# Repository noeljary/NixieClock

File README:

# NixieClock

+ contents

- mcu_code:    firmware for nixie clock micro-controller
- schematics:  eagle circuit schematics and pcb designs including pdf versions
- parts_lists: details of all parts required for circuits

+ description

design and implementation data for the nixie clock project, repository includes data relating to the hardware circuit schematic and board design, supplemented by production gerber files and 3d models

code is available for the microcontroller firmware which runs the interface between the clock ic and the nixie tubes and also for the computer backend which will allow for administrative control of the clock

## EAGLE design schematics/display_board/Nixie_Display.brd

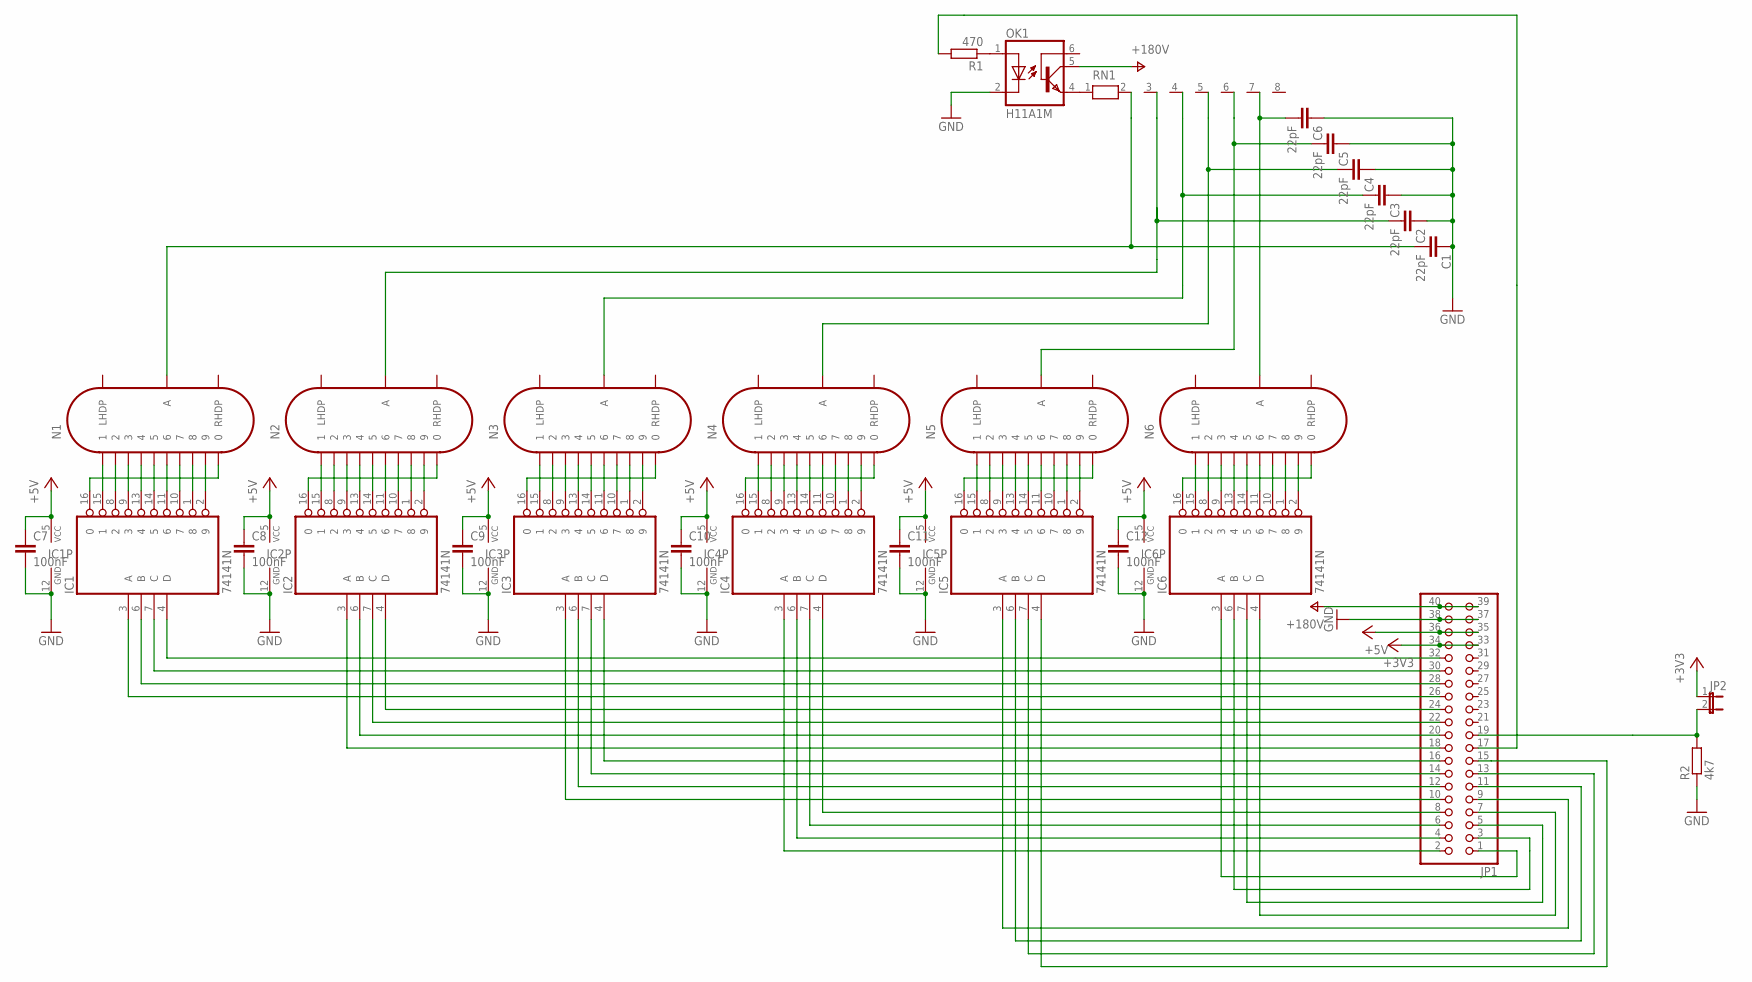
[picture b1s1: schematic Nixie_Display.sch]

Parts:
C1, C2, C3, C4, C5, C6: 22pF; C025-025X050
C7, C8, C9, C10, C11, C12: 100nF; C050-025X075
IC1, IC2, IC3, IC4, IC5, IC6: 74141N; DIL16
JP1: PINHD-2X20; 2X20
JP2: JP1E; JP1
N1, N2, N3, N4, N5, N6: IN-14
OK1: H11A1M; DIL06
R1: 470; 0207/10
R2: 4k7; 0207/10
RN1: RN07; RN-8

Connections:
+3V3: JP1.33, JP1.34, JP2.1
+5V: C7.1, C8.1, C9.1, C10.1, C11.1, C12.1, IC1.5 (VCC), IC2.5 (VCC), IC3.5 (VCC), IC4.5 (VCC), IC5.5 (VCC), IC6.5 (VCC), JP1.35, JP1.36
GND: C1.1, C2.1, C3.1, C4.1, C5.1, C6.1, C7.2, C8.2, C9.2, C10.2, C11.2, C12.2, IC1.12 (GND), IC2.12 (GND), IC3.12 (GND), IC4.12 (GND), IC5.12 (GND), IC6.12 (GND), JP1.37, JP1.38, OK1.2 (C), R2.1
unnamed: IC1.16 (0), N1.0
unnamed: IC1.15 (1), N1.1
unnamed: IC1.8 (2), N1.2
unnamed: IC1.9 (3), N1.3
unnamed: IC1.13 (4), N1.4
unnamed: IC1.14 (5), N1.5
unnamed: IC1.11 (6), N1.6
unnamed: IC1.10 (7), N1.7
unnamed: IC1.1 (8), N1.8
unnamed: IC1.2 (9), N1.9
unnamed: IC2.16 (0), N2.0
unnamed: IC2.15 (1), N2.1
unnamed: IC2.8 (2), N2.2
unnamed: IC2.9 (3), N2.3
unnamed: IC2.13 (4), N2.4
unnamed: IC2.14 (5), N2.5
unnamed: IC2.11 (6), N2.6
unnamed: IC2.10 (7), N2.7
unnamed: IC2.1 (8), N2.8
unnamed: IC2.2 (9), N2.9
unnamed: IC3.16 (0), N3.0
unnamed: IC3.2 (9), N3.9
unnamed: IC3.1 (8), N3.8
unnamed: IC3.10 (7), N3.7
unnamed: IC3.11 (6), N3.6
unnamed: IC3.14 (5), N3.5
unnamed: IC3.13 (4), N3.4
unnamed: IC3.9 (3), N3.3
unnamed: IC3.8 (2), N3.2
unnamed: IC3.15 (1), N3.1
unnamed: IC4.16 (0), N4.0
unnamed: IC4.2 (9), N4.9
unnamed: IC4.1 (8), N4.8
unnamed: IC4.10 (7), N4.7
unnamed: IC4.11 (6), N4.6
unnamed: IC4.14 (5), N4.5
unnamed: IC4.13 (4), N4.4
unnamed: IC4.9 (3), N4.3
unnamed: IC4.8 (2), N4.2
unnamed: IC4.15 (1), N4.1
unnamed: IC5.16 (0), N5.0
unnamed: IC5.2 (9), N5.9
unnamed: IC5.1 (8), N5.8
unnamed: IC5.10 (7), N5.7
unnamed: IC5.11 (6), N5.6
unnamed: IC5.14 (5), N5.5
unnamed: IC5.13 (4), N5.4
unnamed: IC5.9 (3), N5.3
unnamed: IC5.8 (2), N5.2
unnamed: IC5.15 (1), N5.1
unnamed: IC6.16 (0), N6.0
unnamed: IC6.2 (9), N6.9
unnamed: IC6.1 (8), N6.8
unnamed: IC6.10 (7), N6.7
unnamed: IC6.11 (6), N6.6
unnamed: IC6.14 (5), N6.5
unnamed: IC6.13 (4), N6.4
unnamed: IC6.9 (3), N6.3
unnamed: IC6.8 (2), N6.2
unnamed: IC6.15 (1), N6.1
unnamed: IC6.3 (A), JP1.1
unnamed: IC6.6 (B), JP1.3
unnamed: IC6.7 (C), JP1.5
unnamed: IC6.4 (D), JP1.7
unnamed: IC5.3 (A), JP1.9
unnamed: IC5.6 (B), JP1.11
unnamed: IC5.7 (C), JP1.13
unnamed: IC5.4 (D), JP1.15
unnamed: IC4.3 (A), JP1.2
unnamed: IC4.6 (B), JP1.4
unnamed: IC4.7 (C), JP1.6
unnamed: IC4.4 (D), JP1.8
unnamed: OK1.4 (EMI), RN1.1
unnamed: IC3.3 (A), JP1.10
unnamed: IC3.6 (B), JP1.12
unnamed: C6.2, N6.A, RN1.7
unnamed: IC3.7 (C), JP1.14
unnamed: IC3.4 (D), JP1.16
unnamed: IC2.3 (A), JP1.18
unnamed: IC2.6 (B), JP1.20
unnamed: IC2.7 (C), JP1.22
unnamed: IC2.4 (D), JP1.24
unnamed: IC1.4 (D), JP1.32
unnamed: IC1.7 (C), JP1.30
unnamed: C5.2, N5.A, RN1.6
unnamed: C4.2, N4.A, RN1.5
unnamed: C3.2, N3.A, RN1.4
unnamed: C2.2, N2.A, RN1.3
unnamed: C1.2, N1.A, RN1.2
unnamed: JP1.17, R1.2
unnamed: OK1.1 (A), R1.1
unnamed: IC1.6 (B), JP1.28
unnamed: IC1.3 (A), JP1.26
unnamed: JP1.19, JP2.2, R2.2
V+: JP1.39, JP1.40, OK1.5 (COL)

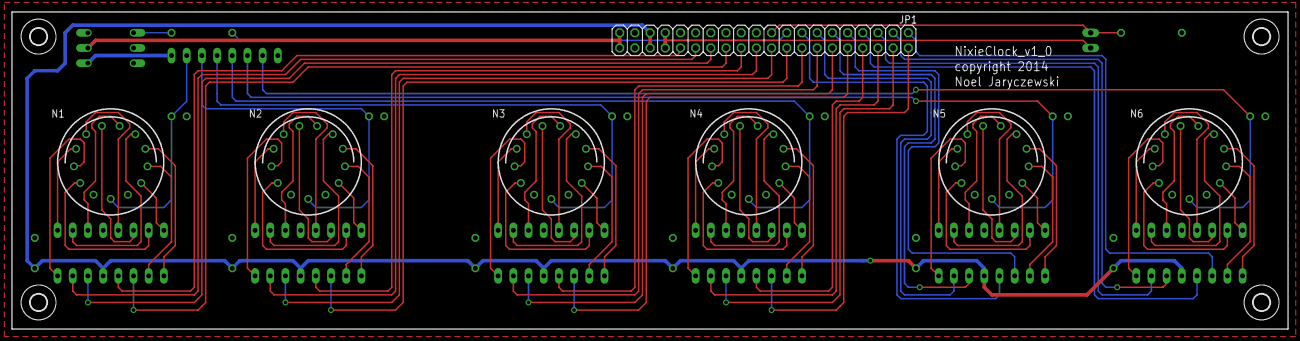
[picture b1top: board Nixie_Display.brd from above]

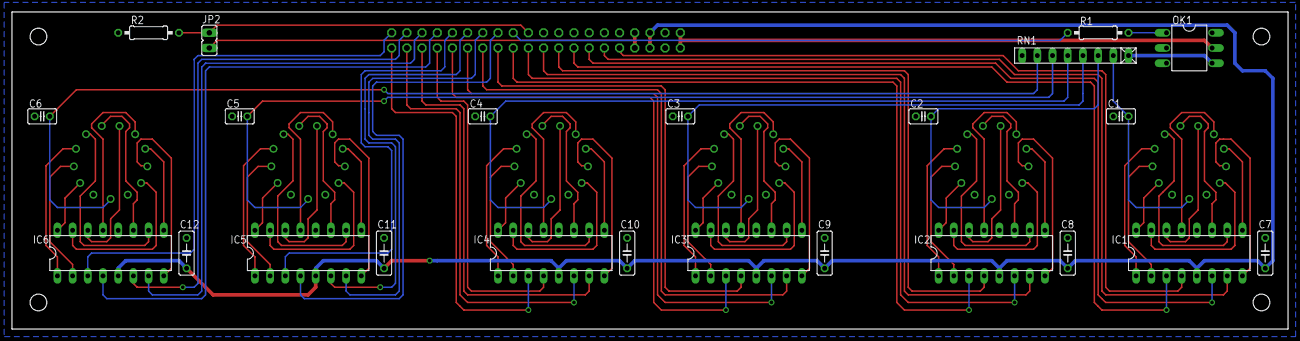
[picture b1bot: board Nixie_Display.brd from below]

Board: 2 copper layers, 213.3 x 53.0 mm, 34 parts (23 on the bottom side), 98 nets.

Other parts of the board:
U$1, U$2, U$3, U$4: 2,8

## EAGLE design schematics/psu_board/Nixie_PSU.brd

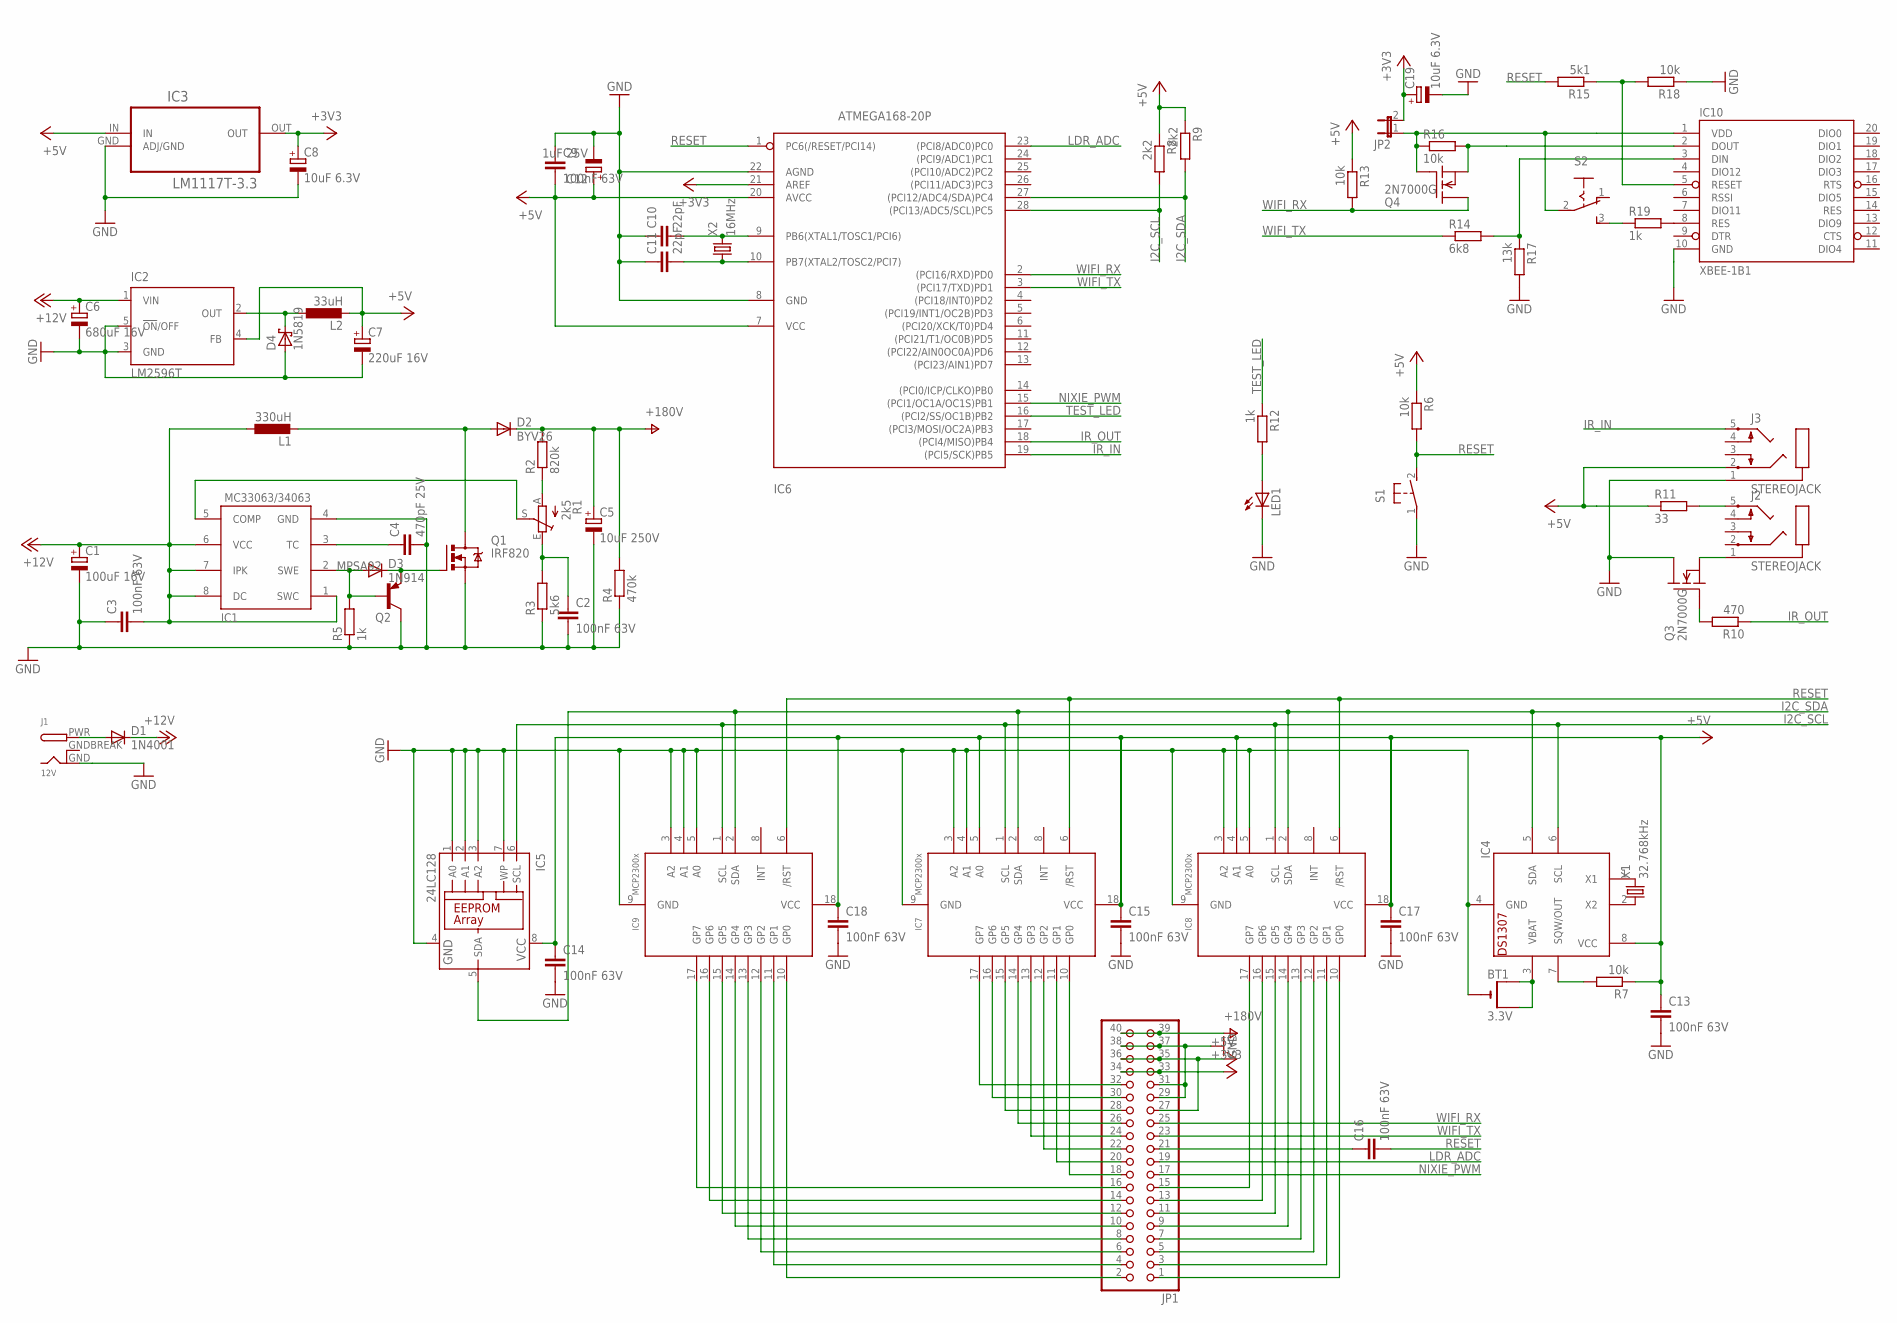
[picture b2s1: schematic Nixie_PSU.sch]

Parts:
BT1: 3.3V; CR1220-THM
C1: 100uF 16V; E2-5
C2, C3, C9, C13, C14, C15, C16, C17, C18: 100nF 63V; C050-025X075
C4: 470pF 25V; C025-025X050
C5: 10uF 250V; E5-10,5
C6: 680uF 16V; E3,5-8
C7: 220uF 16V; E2,5-7
C8, C19: 10uF 6.3V; E5-4
C10, C11: 22pF; C025-025X050
C12: 1uF 25V; E5-4
D1: 1N4001; DO41-10
D2: BYV26; SOD57-10
D3: 1N914; DO34-7
D4: 1N5819; DO41-10
IC1: MC33063/MC34063P; DIL08
IC2: LM2596T; T05D
IC3: LM1117T-3.3; TO220BV
IC4: DS1307; DIL08
IC5: 24LC128; DIL08
IC6: ATMEGA168-20P; DIL28-3
IC7, IC8, IC9: MCP2300X/P; DIL18
IC10: XBEE-1B1; XBEE-1
J1: 12V; DCJACK_2MM_PTH
J2, J3: STEREOJACK; STX3100
JP1: PINHD-2X20; 2X20
JP2: JP1E; JP1
L1: 330uH; 0207/5V
L2: 33uH; 0207/5V
LED1: LED5MM
Q1: IRF820; TO220BV
Q2: MPSA92; TO92
Q3, Q4: 2N7000G; TO-92
R1: 2k5; RJ9W
R2: 820k; 0207/10
R3: 5k6; 0207/10
R4: 470k; 0207/10
R5, R12, R19: 1k; 0207/10
R6, R7, R13, R16, R18: 10k; 0207/10
R8, R9: 2k2; 0207/10
R10: 470; 0207/10
R11: 33; 0207/10
R14: 6k8; 0207/10
R15: 5k1; 0207/10
R17: 13k; 0207/10
S1: 31-XX; B3F-31XX
S2: M251
X1: 32.768kHz; TC38H
X2: 16MHz; HC18U-V

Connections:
+3V3: C8.+, C19.+, IC3.OUT, IC6.21 (AREF), JP1.33, JP1.34, JP2.2
+5V: C7.+, C9.2, C12.+, C13.1, C14.1, C15.1, C17.1, C18.1, IC2.4 (FB), IC3.IN, IC4.8 (VCC), IC5.8 (VCC), IC6.7 (VCC), IC6.20 (AVCC), IC7.5 (A0), IC7.18 (VCC), IC8.4 (A1), IC8.18 (VCC), IC9.18 (VCC), J3.2, JP1.27, JP1.35, JP1.36, L2.2, R6.1, R7.1, R8.1, R9.1, R11.1, R13.1
+12V: C1.+, C3.2, C6.+, D1.C, IC1.1 (SWC), IC1.6 (VCC), IC1.7 (IPK), IC1.8 (DC), IC2.1 (VIN), L1.1
GND: BT1.-, C1.-, C2.2, C3.1, C4.2, C5.-, C6.-, C7.-, C8.-, C9.1, C10.1, C11.1, C12.-, C13.2, C14.2, C15.2, C17.2, C18.2, C19.-, D4.A, IC1.4 (GND), IC2.3 (GND), IC2.5 (!ON!/OFF), IC3.GND (ADJ/GND), IC4.4 (GND), IC5.1 (A0), IC5.2 (A1), IC5.3 (A2), IC5.4 (GND), IC5.7 (WP), IC6.8 (GND), IC6.22 (AGND), IC7.3 (A2), IC7.4 (A1), IC7.9 (GND), IC8.3 (A2), IC8.5 (A0), IC8.9 (GND), IC9.3 (A2), IC9.4 (A1), IC9.5 (A0), IC9.9 (GND), IC10.10 (GND), J1.GND, J3.1, JP1.29, JP1.31, JP1.37, JP1.38, LED1.K (C), Q1.S, Q2.3 (C), Q3.3 (D), R3.1, R4.1, R5.1, R17.2, R18.1, S1.1
GNDBREAK: J1.GNDBREAK
I2C_SCL: IC4.6 (SCL), IC5.6 (SCL), IC6.28 ((PCI13/ADC5/SCL)PC5), IC7.1 (SCL), IC8.1 (SCL), IC9.1 (SCL), R8.2
I2C_SDA: IC4.5 (SDA), IC5.5 (SDA), IC6.27 ((PCI12/ADC4/SDA)PC4), IC7.2 (SDA), IC8.2 (SDA), IC9.2 (SDA), R9.2
IR_IN: IC6.19 ((PCI5/SCK)PB5), J3.5
IR_OUT: IC6.18 ((PCI4/MISO)PB4), R10.1
LDR_ADC: IC6.23 ((PCI8/ADC0)PC0), JP1.19
unnamed: C4.1, IC1.3 (TC)
unnamed: D3.A, IC1.2 (SWE), Q2.2 (B), R5.2
unnamed: D2.A, L1.2, Q1.D
unnamed: C16.1, JP1.21
unnamed: IC1.5 (COMP), R1.S
unnamed: Q3.2 (G), R10.2
unnamed: J2.1, Q3.1 (S)
unnamed: IC10.1 (VDD), JP2.1, Q4.2 (G), R16.1, S2.2
unnamed: C11.2, IC6.10 (PB7(XTAL2/TOSC2/PCI7)), X2.1
unnamed: C10.2, IC6.9 (PB6(XTAL1/TOSC1/PCI6)), X2.2
unnamed: IC4.1 (X1), X1.2
unnamed: IC4.2 (X2), X1.1
unnamed: BT1.+1 (+), BT1.+2 (+1), IC4.3 (VBAT)
unnamed: IC4.7 (SQW/OUT), R7.2
unnamed: IC9.10 (GP0), JP1.2
unnamed: D4.C, IC2.2 (OUT), L2.1
unnamed: IC9.11 (GP1), JP1.4
unnamed: IC9.12 (GP2), JP1.6
unnamed: IC9.13 (GP3), JP1.8
unnamed: IC9.14 (GP4), JP1.10
unnamed: IC9.15 (GP5), JP1.12
unnamed: IC9.16 (GP6), JP1.14
unnamed: IC9.17 (GP7), JP1.16
unnamed: IC7.10 (GP0), JP1.18
unnamed: IC7.11 (GP1), JP1.20
unnamed: IC7.12 (GP2), JP1.22
unnamed: IC7.13 (GP3), JP1.24
unnamed: IC7.14 (GP4), JP1.26
unnamed: IC7.15 (GP5), JP1.28
unnamed: IC7.16 (GP6), JP1.30
unnamed: IC7.17 (GP7), JP1.32
unnamed: IC8.10 (GP0), JP1.1
unnamed: IC8.11 (GP1), JP1.3
unnamed: IC8.12 (GP2), JP1.5
unnamed: IC8.13 (GP3), JP1.7
unnamed: IC8.14 (GP4), JP1.9
unnamed: IC8.15 (GP5), JP1.11
unnamed: IC8.16 (GP6), JP1.13
unnamed: IC8.17 (GP7), JP1.15
unnamed: R19.1, S2.3 (S)
unnamed: IC10.5 (RESET), R15.1, R18.2
unnamed: D3.C, Q1.G, Q2.1 (E)
unnamed: LED1.A, R12.2
unnamed: J2.5, R11.2
unnamed: IC10.8 (RES), R19.2
unnamed: C2.1, R1.E, R3.2
unnamed: R1.A, R2.1
unnamed: IC10.2 (DOUT), Q4.1 (S), R16.2
unnamed: IC10.3 (DIN), R14.2, R17.1
NIXIE_PWM: IC6.15 ((PCI1/OC1A/OC1S)PB1), JP1.17
PWR: D1.A, J1.PWR
RESET: C16.2, IC6.1 (PC6(/RESET/PCI14)), IC7.6 (/RST), IC8.6 (/RST), IC9.6 (/RST), R6.2, R15.2, S1.2 (S)
TEST_LED: IC6.16 ((PCI2/SS/OC1B)PB2), R12.1
V+: C5.+, D2.C, JP1.39, JP1.40, R2.2, R4.2
WIFI_RX: IC6.2 ((PCI16/RXD)PD0), JP1.25, Q4.3 (D), R13.2
WIFI_TX: IC6.3 ((PCI17/TXD)PD1), JP1.23, R14.1

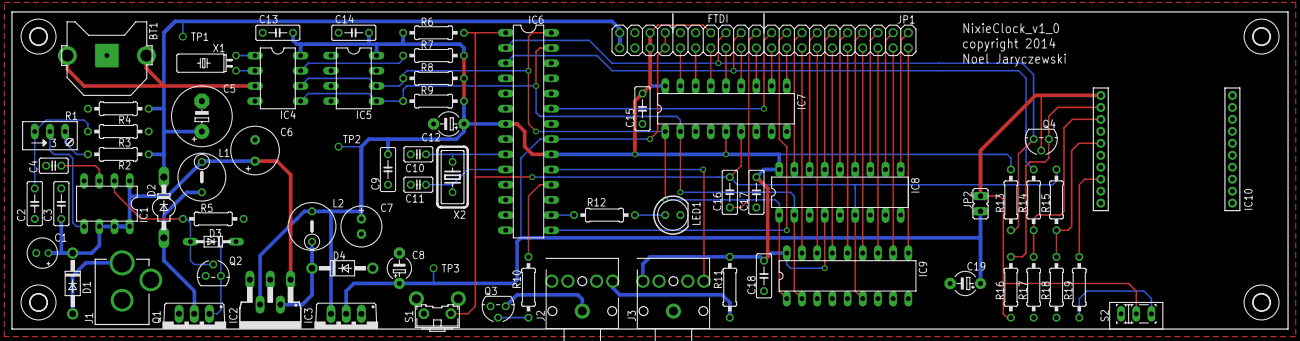
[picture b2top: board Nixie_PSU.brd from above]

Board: 2 copper layers, 213.3 x 53.0 mm, 73 parts (0 on the bottom side), 65 nets.

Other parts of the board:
U$1, U$3, U$4, U$5: 2,8

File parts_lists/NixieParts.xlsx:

Part Number | Value
R1 | 2k5 | Cermet | ±
R2 | 820k |  | ±
R3 | 5k6 |  | ±
R4 | 470k |  | ±
R5,12,19 | 1k |  | ±
R6,7,13,16-18 | 10k |  | ±
R8,9 | 2k2 |  | ±
R10 | 470 |  | ±
R11 | 33 |  | ±
R14-15 | 5k1 |  | ±
C1 | 100u 16V |  | ±
C2,3,9,13-18 | 100n 63V |  | ±
C4 | 470p 25V |  | ±
C5 | 10u 250V |  | ±
C6 | 680u 16V |  | ±
C7 | 220u 16V |  | ±
C8,19 | 10u 6.3V | Tantalum | ±
C10,11 | 22p |  | ±
C12 | 1u 25V | Tantalum | ±
D1 | 1N4001 |  | ±
D2 | BYV26 |  | ±
D3 | 1N914 |  | ±
D4 | 1N5819 |  | ±
IC1 | MC34063 |  | ±
IC2 | LM2596 |  | ±
IC3 | LM1117 |  | ±
IC4 | DS1307 |  | ±
IC5 | 24LC128 |  | ±
IC6 | AtMega 328P |  | ±
IC7-9 | MCP23008 |  | ±
IC10 | WiFly
J1 | DC Jack 2.1mm |  | ±
J2,3 | Stereo Jack 3.5mm |  | ±
JP1 | 2x20 Pin Header |  | ±
JP2 | 1x2 Pin Header |  | ±
L1 | 330u |  | ±
L2 | 33u |  | ±
Q1 | IRF820 |  | ±
Q2 | MPSA92 |  | ±
Q3,4 | 2N7000 |  | ±
X1 | 32.768MHz |  | ±
X2 | 16MHz |  | ±
SW1 | 90Deg PCB Mount |  | ±
SW2 | Slide Switch |  | ±
BT1 | CR1220 Cage
LED1 | 5mm Red |  | ±

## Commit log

2014-02-22 Add README file for Nixie Clock Project
2014-02-22 Initial commit of project structure and mcu firmware
2014-02-22 Complete circuit schematics, board designs, pdf versions, gerber files and 3d model
2014-02-26 Updated project readme file
2014-02-26 Added project description
2021-07-03 Add Parts List

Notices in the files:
schematics/display_board/Nixie_Display.brd:
copyright 2014
parts and their libraries:
SparkFun: Licensing: CC v3.0 Share-Alike You are welcome to use this library for commercial purposes.
